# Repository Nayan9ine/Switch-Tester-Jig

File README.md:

# Switch-Tester-Jig
<div align="right"><i>-by Nayan Ag</i></div>
<br>
Created a switch testing jig using Arduino UNO which tests the electrical durability of contact in scooty switches. 
<br><br>
This is a project that I created during my internship in a 2 wheeler EV startup company. The handle-bar switch assembly are fitted by various switches that the company imports from different vendors. Since it's a startup company we experimented by ordering from different vendors for the same switch. This project was made to test the durability of those.
<br><br>
The various types of switches that were tested are: Horn, Upper-Dipper, Ignition, Reverse.
<br>
Components used: A switch and motor holder,L298N motor controller, two 16X2 I2C LCD, arduino uno, jumper cables,cam to press the button, Switch coupler,12v battery to run motor, Switch for manual control.
<br>
The cam and holder for switches was made by senior.
<br><br>
<table>
  <tr>
    <td>
    <br>  <div  align="center"><sub><i> Fig1:Jig with cam and switch installed</i></sub></div>
</td>
    <td>
    <br>  <div  align="center"><sub><i> Fig2:motor fitting location</i></sub></div>
</td>
    <td>
    <br><div align="center"><sub><i> Fig3:back side</i></sub></div>
</td>
  </tr>
</table>
<br><br>
<table>
  <tr>
    <td>
    <br>  <div  align="center"><sub><i> Fig4:Arduino UNO</i></sub></div>
</td>
    <td>
    <br>  <div  align="center"><sub><i> Fig5:2 LCDs</i></sub></div>
</td>
    <td>
    <br><div align="center"><sub><i> Fig6:12v Battery & ON-OFF Switch for manual control</i></sub></div>
</td>
  </tr>
</table>
<br>
<table>
  <tr>
    <td>
    <br>  <div  align="center"><sub><i> Fig7:Arduino UNO</i></sub></div>
</td>
    <td>
    <br>  <div  align="center"><sub><i> Fig8:Switches</i></sub></div>
</td>
    <td>
    <br><div align="center"><sub><i> Fig9:12v DC Motor</i></sub></div>
</td>
  </tr>
</table>
<br>
<table>
  <tr>
    <td>
    <br>  <div  align="center"><sub><i> Fig10:Switch Pinout</i></sub></div>
</td>
    <td>
    <br>  <div  align="center"><sub><i> Fig11:Overall Setup</i></sub></div>
</td>
  </tr>
</table>
<br><br>
Drive link for working video: https://drive.google.com/drive/folders/12oiliMJjxmbsB1hyvkpnEl2Vyk8v8IB5?usp=sharing
<br><br>
<table>
  <tr>
    <td>
  <br>  <div  align="center"><sub><i> Fig12:Schematic with ERC</i></sub></div>
</td>
    <td>
    <br>  <div  align="center"><sub><i> Fig13:PCB editor DRC check</i></sub></div>
</td>
    <td>
    <br>  <div  align="center"><sub><i> Fig14:PCB editor Full view</i></sub></div>
</td>
  </tr>
</table>
<br>
<table>
  <tr>
    <td>
  <br>  <div  align="center"><sub><i> Fig15:3D Front</i></sub></div>
</td>
    <td>
    <br>  <div  align="center"><sub><i> Fig16:3D Side</i></sub></div>
</td>
    <td>
    <br>  <div  align="center"><sub><i> Fig17:3D Back</i></sub></div>
</td>
  </tr>
</table>

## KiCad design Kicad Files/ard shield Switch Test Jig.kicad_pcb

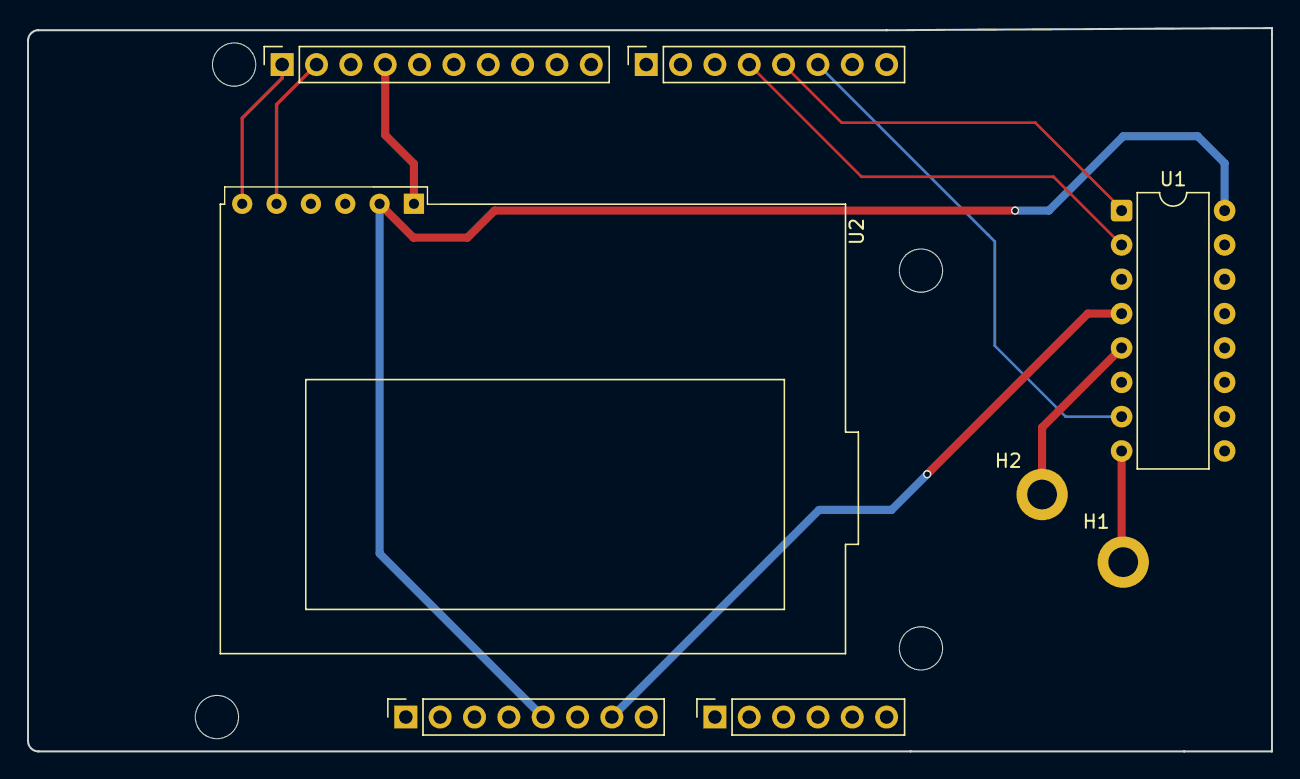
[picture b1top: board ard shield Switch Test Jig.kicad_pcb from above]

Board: 2 copper layers, 92.0 x 53.5 mm, 12 parts (0 on the bottom side), 10 nets.

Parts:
H1: +12v; MountingHole_2.2mm_M2_DIN965_Pad
H2: 0v; MountingHole_2.2mm_M2_DIN965_Pad
J1: Power; PinSocket_1x08_P2.54mm_Vertical
J2: Digital/PWM; PinSocket_1x10_P2.54mm_Vertical
J3: Analog; PinSocket_1x06_P2.54mm_Vertical
J4: Digital/PWM; PinSocket_1x08_P2.54mm_Vertical
MH1, MH2, MH3, MH4: MountingHole_3.2mm
U1: L293D; DIP-16_W7.62mm
U2: EA_T123X-I2C

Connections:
/2: J4.6, U1.7 (2A)
/4: J4.4, U1.2 (1A)
/5v: J1.5, U1.16 (VCC1), U2.2 (VDD)
/*3: J4.5, U1.1 (EN1,2)
/SCL/A5: J2.1, U2.6 (SCL)
/SDA/A4: J2.2, U2.5 (SDA)
GND: J1.7, U1.4 (GND)
GND2: J2.4, U2.1 (VSS)
unnamed: H2.1, U1.5 (GND)
unnamed: H1.1, U1.8 (VCC2)
